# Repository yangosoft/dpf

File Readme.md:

# Diesel Filter Particle viewer

Only tested in a Volkswagen 2.0 TDI CAGA engine.

The code is mostly based on https://github.com/fkoca5055/obdESP with some changes to check DFP status, provide a WiFi Access Point to change Bluetooth device, PIN, debug viewer...

Please note: as I'm not having so much time to spend on this project the code is quick and dirty.

## Needed parts

 - ESP32 NodeMCU ESP-32s
 - TFT Screen based on ILI9341
 - ELM327 Bluetooth

## Box and schema

 - [PCB](schema/dpf1) designed with EAGLE.
 - [Box to 3d print](schema/3dmodel) designed with FreeCAD.

## Pinout

|  TFT |   ESP32 GPIO |
|---|---|
| TFT_CS | 15 |
| TFT_DC | 4 |
| TFT_MOSI | 23 |
| TFT_SLK | 18 |
| TFT_RST | 2 |
| TFT_LED | -1 |
| TFT_MISO | 19 |

Please change `TFT_RST` to another GPIO since this the integrated led in `NodeMCU ESP-32s`.

# Next steps

Remove the screen and make use of the FIS to display DFP information

# Useful links

- https://stackoverflow.com/questions/23877761/sniffing-logging-your-own-android-bluetooth-traffic
- https://forums.tdiclub.com/index.php?threads/reading-soot-level-with-torque.464119/page-4
- https://github.com/fkoca5055/obdESP/blob/master/2.4_LCD.ino
- https://www.cardumps.net/account/my-profile
- https://stackoverflow.com/questions/23877761/sniffing-logging-your-own-android-bluetooth-traffic
- http://jakubdziworski.github.io/obd/bluetooth/arduino/car/2020/07/13/arduino-obd-dpf-monitor-insignia.html
- http://www.areavag.com/foro/showthread.php?42159-Regeneraci%F3n-filtro-part%EDculas-diagnosis-con-iPhone/page3
- https://gist.github.com/0/c73e2557d875446b9603
- https://stackoverrun.com/es/q/12573350
- http://jakubdziworski.github.io/
- https://scribles.net/setting-up-bluetooth-serial-port-profile-on-raspberry-pi/
- https://forum.fairphone.com/t/location-of-btsnoop-hci-log-file/60320
- https://www.fte.com/WebHelpII/Sodera/Content/Documentation/WhitePapers/BPA600/Encryption/GettingAndroidLinkKey/RetrievingHCIlog.htm
- https://stackoverflow.com/questions/23877761/sniffing-logging-your-own-android-bluetooth-traffic
- https://github.com/fkoca5055/obdESP
- https://github.com/ibanezgomez/FISBlocks

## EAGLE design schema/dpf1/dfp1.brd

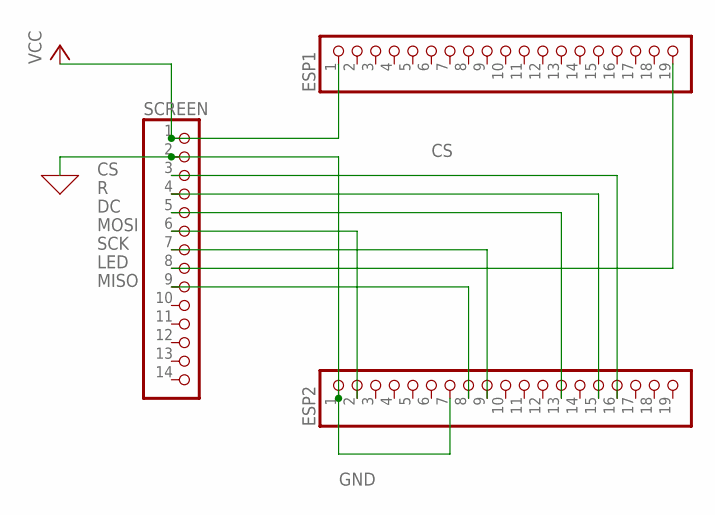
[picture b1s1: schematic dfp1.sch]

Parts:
ESP1, ESP2: PINHD-1X19; 1X19
SCREEN: PINHD-1X14; 1X14

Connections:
CS: ESP2.16, SCREEN.3
DC: ESP2.13, SCREEN.5
GND: ESP2.1, ESP2.7, SCREEN.2
LED: ESP1.19, SCREEN.8
MISO: ESP2.8, SCREEN.9
MOSI: ESP2.2, SCREEN.6
R: ESP2.15, SCREEN.4
SCK: ESP2.9, SCREEN.7
VCC: ESP1.1, SCREEN.1

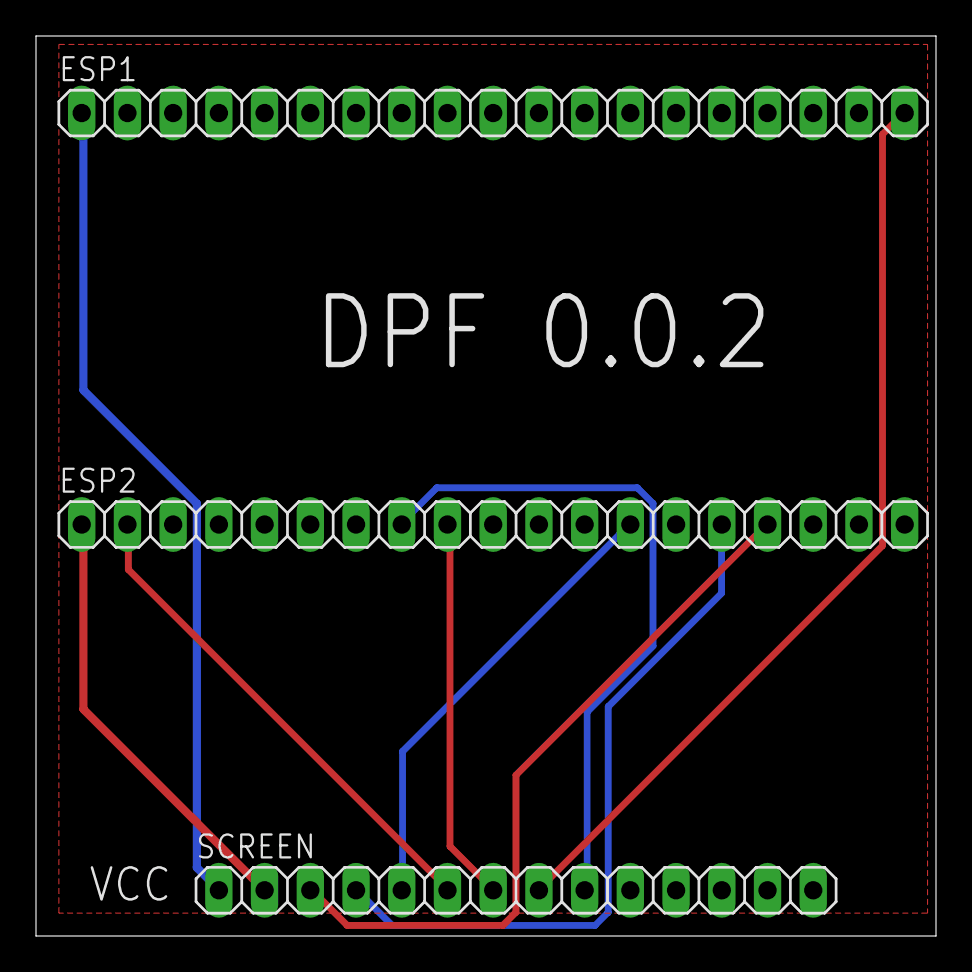
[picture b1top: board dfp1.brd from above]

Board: 2 copper layers, 50.0 x 50.0 mm, 3 parts (0 on the bottom side), 9 nets.

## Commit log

2020-11-25 Added Readme
2020-11-25 Added missing partition table
2020-11-26 Removed oil temp
2020-11-26 Fixed wrong comment
2020-11-26 Create main.yml
    Action to run platformio
2020-11-26 Added some images
2020-12-01 New images
2020-12-02 Added new box and images
